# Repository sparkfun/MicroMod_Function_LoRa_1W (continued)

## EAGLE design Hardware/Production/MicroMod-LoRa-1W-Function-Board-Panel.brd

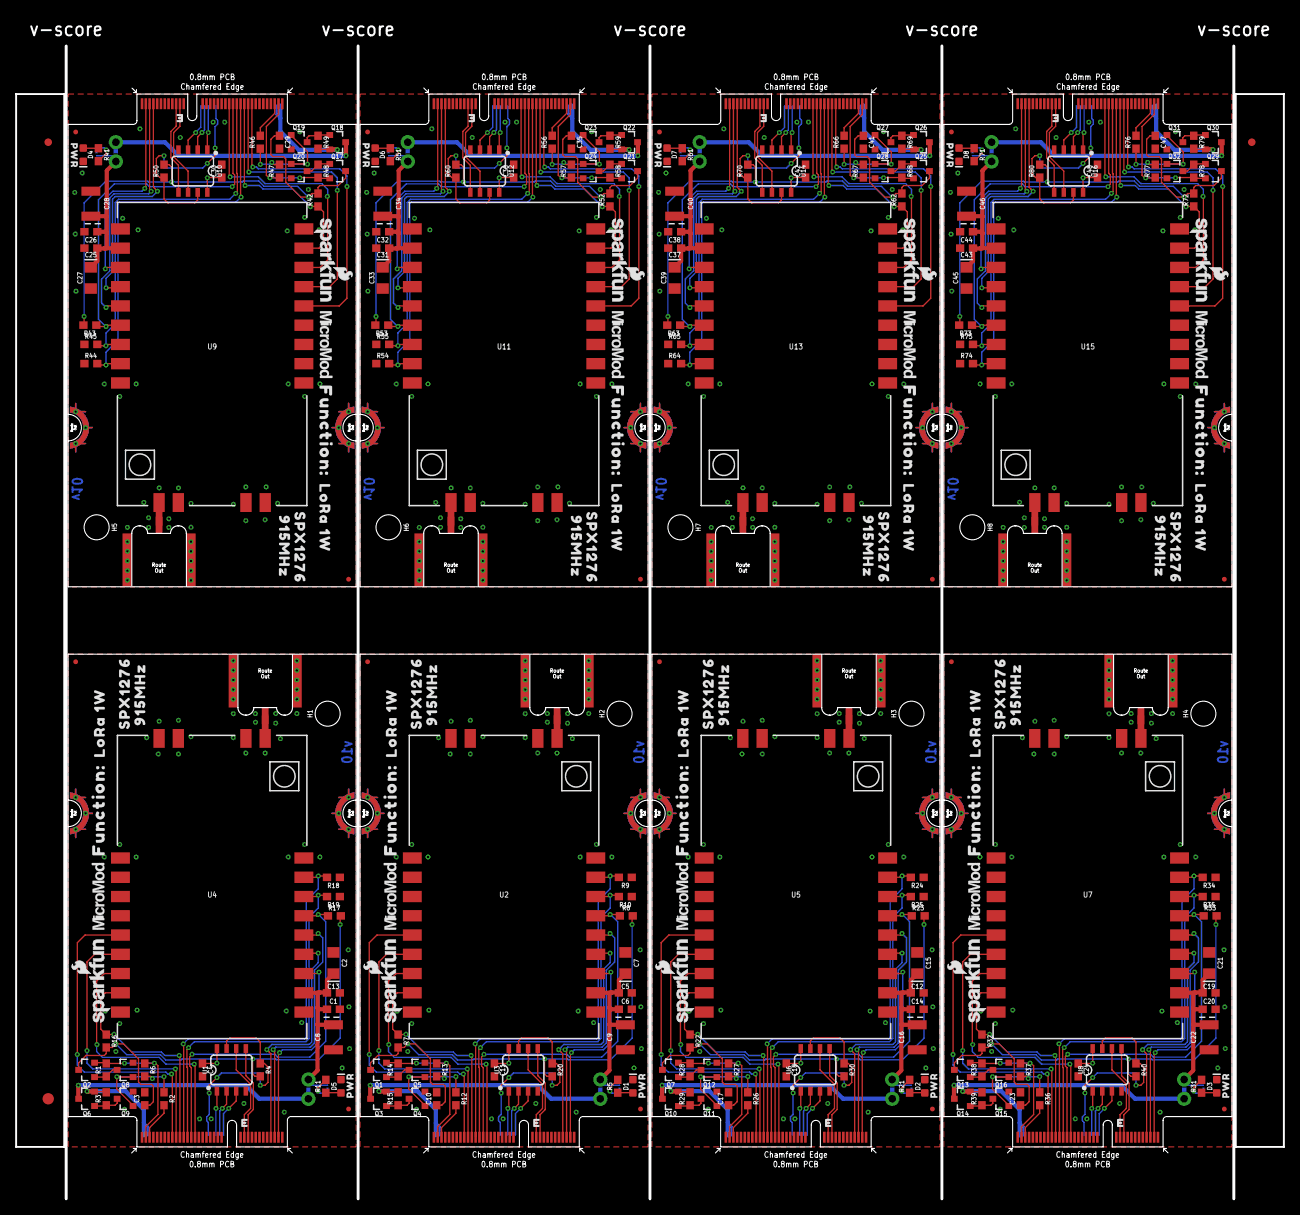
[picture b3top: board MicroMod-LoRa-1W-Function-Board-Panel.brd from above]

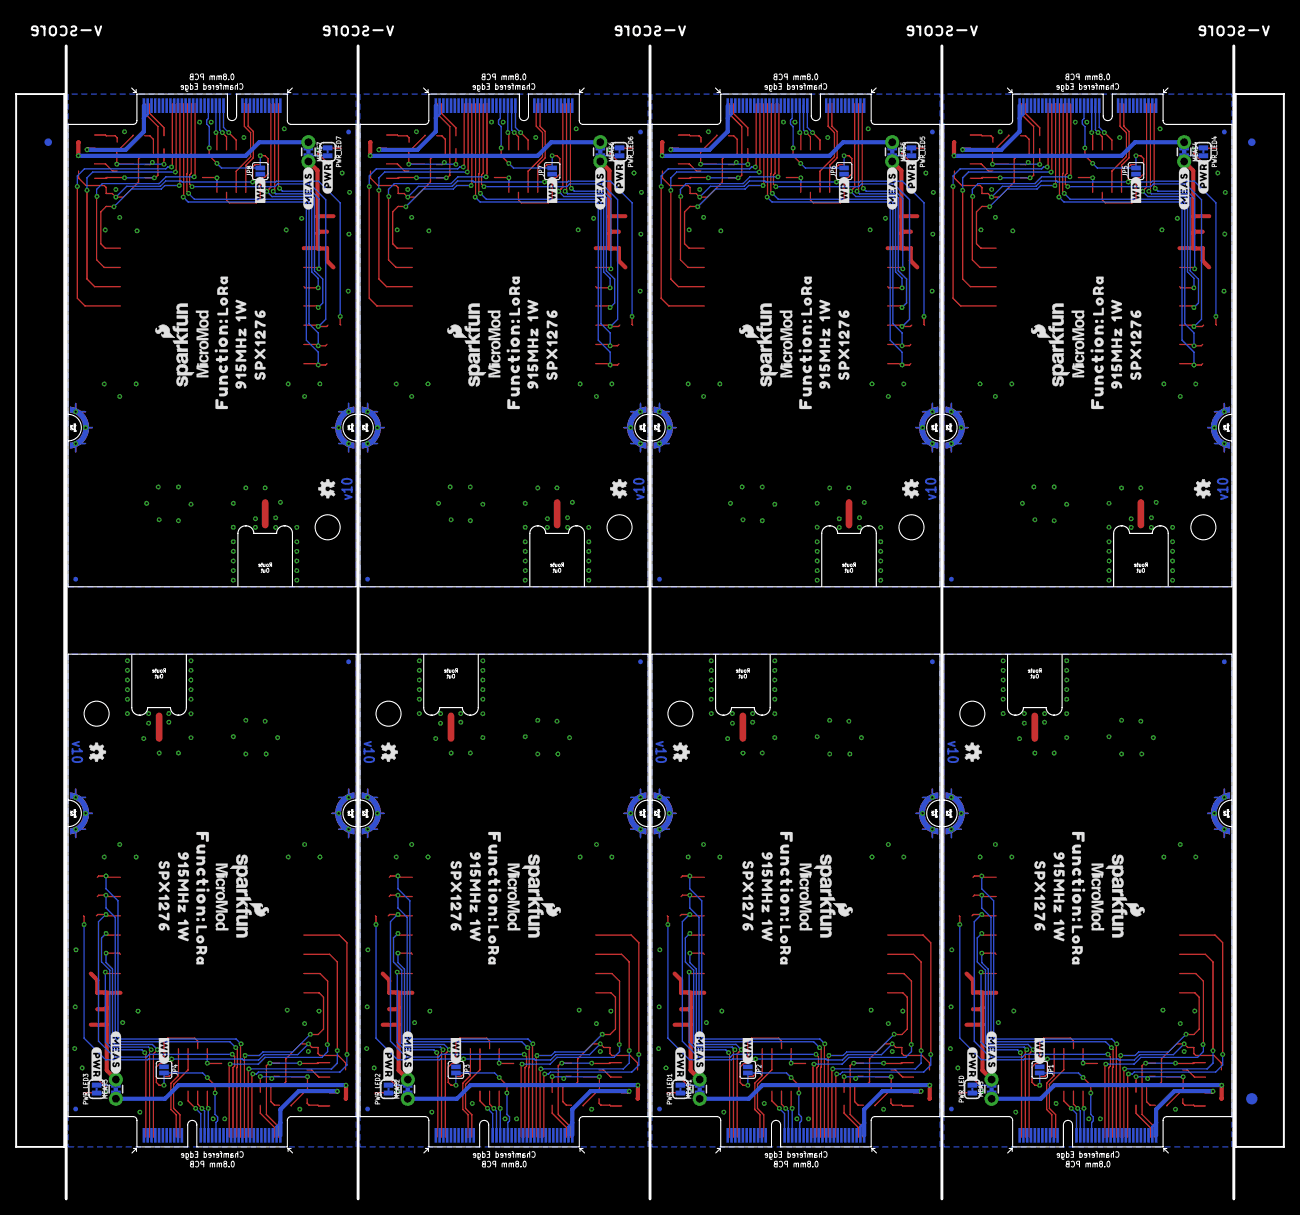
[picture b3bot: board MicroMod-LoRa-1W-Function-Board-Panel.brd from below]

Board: 2 copper layers, 167.1 x 156.0 mm, 422 parts (131 on the bottom side), 232 nets.

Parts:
C1, C3, C4, C6, C10, C11, C14, C17, C18, C20, C23, C24, C26, C29, C30, C32, C35, C36, C38, C41, C42, C44, C47, C48: 0.1uF; 0603
C2, C7, C15, C21, C27, C33, C39, C45: 10uF; EIA3216
C5, C12, C13, C19, C25, C31, C37, C43: 0.22uF; 0603
C8, C9, C16, C22, C28, C34, C40, C46: 47uF; EIA3528
D1, D2, D3, D4, D5, D6, D7, D8: RED; LED-0603
E1, E2, E3, E4, E5, E6, E7, E8: RP-SMA; SMA-EDGE-SMD
E$1, E$2, E$3, E$4: FIDUCIAL-1X2
E$5, E$6: FIDUCIAL-1.5X3
FD1, FD2, FD3, FD4, FD5, FD6, FD7, FD8, FD9, FD10, FD11, FD12, FD13, FD14, FD15, FD16, FD17, FD18, FD19, FD20, FD21, FD22, FD23, FD24, FD25, FD26, FD27, FD28, FD29, FD30, FD31, FD32: FIDUCIALUFIDUCIAL; FIDUCIAL-MICRO
H1, H2, H3, H4, H5, H6, H7, H8: STAND-OFF
J1, J2, J3, J4, J5, J6, J7, J11: MICROMOD_STANDARD; M.2-CARD-E-22_FUNCTION_STANDARD
JP1, JP2, JP3, JP4, JP5, JP6, JP7, JP8: JUMPER-SMT_2_NO_SILK; SMT-JUMPER_2_NO_SILK
LOGO1, LOGO2, LOGO4, LOGO6, LOGO7, LOGO9, LOGO10, LOGO12, LOGO13, LOGO15, LOGO16, LOGO18, LOGO19, LOGO21, LOGO22, LOGO24: SFE_LOGO_NAME_FLAME.1_INCH; SFE_LOGO_NAME_FLAME_.1
LOGO3, LOGO5, LOGO8, LOGO11, LOGO14, LOGO17, LOGO20, LOGO23: OSHW-LOGOMINI; OSHW-LOGO-MINI
MEAS, MEAS1, MEAS2, MEAS3, MEAS4, MEAS5, MEAS6, MEAS7: JUMPER-COMBO_2_NC_TRACE; COMBO-JUMPER_2_NC_TRACE
PWR_LED, PWR_LED1, PWR_LED2, PWR_LED3, PWR_LED4, PWR_LED5, PWR_LED6, PWR_LED7: JUMPER-SMT_2_NC_TRACE_SILK; SMT-JUMPER_2_NC_TRACE_SILK
Q1, Q2, Q3, Q6, Q7, Q10, Q13, Q14, Q17, Q18, Q21, Q22, Q25, Q26, Q29, Q30: 20V/4.2A/52mΩ/1.4W; SOT23-3
Q4, Q5, Q8, Q9, Q11, Q12, Q15, Q16, Q19, Q20, Q23, Q24, Q27, Q28, Q31, Q32: 5.8A/30V/35mΩ; SOT23-3
R1, R3, R4, R14, R15, R20, R28, R29, R30, R38, R39, R40, R48, R49, R50, R58, R59, R60, R68, R69, R70, R78, R79, R80: 10k; 0603
R2, R12, R26, R36, R46, R56, R66, R76: 470; 0603
R5, R11, R21, R31, R41, R51, R61, R71: 1k; 0603
R6, R7, R8, R9, R10, R13, R16, R17, R18, R19, R22, R23, R24, R25, R27, R32, R33, R34, R35, R37, R42, R43, R44, R45, R47, R52, R53, R54, R55, R57, R62, R63, R64, R65, R67, R72, R73, R74, R75, R77: 100k; 0603
U1, U3, U6, U8, U10, U12, U14, U16: EEPROM; SO08
U2, U4, U5, U7, U9, U11, U13, U15: E19-915M30S; E19-915MS1W
U$1, U$5, U$16, U$19, U$36, U$40, U$53, U$56, U$70, U$73, U$86, U$89, U$102, U$105, U$118, U$121: LORA0
U$2, U$14, U$22, U$30, U$34, U$43, U$51, U$59, U$68, U$76, U$84, U$92, U$100, U$108, U$116, U$124: 1W1
U$3, U$15, U$21, U$29, U$35, U$42, U$52, U$58, U$69, U$75, U$85, U$91, U$101, U$107, U$117, U$123: 915MHZ2
U$4, U$8, U$23, U$25, U$44, U$46, U$60, U$62, U$77, U$79, U$93, U$95, U$109, U$111, U$125, U$127: FUNCTION#0
U$6, U$17, U$20, U$27, U$38, U$41, U$54, U$57, U$71, U$74, U$87, U$90, U$103, U$106, U$119, U$122: SPX12763
U$7, U$18, U$39, U$55, U$72, U$88, U$104, U$120: PWR0
U$9, U$24, U$45, U$61, U$78, U$94, U$110, U$126: #PWR#0
U$10, U$26, U$47, U$64, U$80, U$96, U$112, U$128: #WP#0
U$11, U$12, U$31, U$32, U$37, U$48, U$49, U$63, U$65, U$66, U$81, U$82, U$97, U$98, U$113, U$114: MICROMOD_LOGO_.35
U$13, U$28, U$33, U$50, U$67, U$83, U$99, U$115: #MEAS#3

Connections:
3.3V: C3.1, C4.1, Q2.3, R4.2, R16.2, R17.2, U1.8
3.3V1: C10.1, C11.1, Q1.3, R7.2, R8.2, R20.2, U3.8
3.3V2: C17.1, C18.1, Q7.3, R22.2, R23.2, R30.2, U6.8
3.3V3: C23.1, C24.1, Q13.3, R32.2, R33.2, R40.2, U8.8
3.3V4: C29.1, C30.1, Q17.3, R42.2, R43.2, R50.2, U10.8
3.3V5: C35.1, C36.1, Q21.3, R52.2, R53.2, R60.2, U12.8
3.3V6: C41.1, C42.1, Q25.3, R62.2, R63.2, R70.2, U14.8
3.3V7: C47.1, C48.1, Q29.3, R72.2, R73.2, R80.2, U16.8
3.3V_IN: J11.73, Q2.2, R1.2, R6.1
3.3V_IN1: J1.73, Q1.2, R13.1, R14.2
3.3V_IN2: J2.73, Q7.2, R27.1, R28.2
3.3V_IN3: J3.73, Q13.2, R37.1, R38.2
3.3V_IN4: J4.73, Q17.2, R47.1, R48.2
3.3V_IN5: J5.73, Q21.2, R57.1, R58.2
3.3V_IN6: J6.73, Q25.2, R67.1, R68.2
3.3V_IN7: J7.73, Q29.2, R77.1, R78.2
5V: C1.1, C2.+, C8.A, C13.1, MEAS.2, MEAS.4, PWR_LED.2, U4.11
5V1: C5.1, C6.1, C7.+, C9.A, MEAS1.2, MEAS1.4, PWR_LED1.2, U2.11
5V2: C12.1, C14.1, C15.+, C16.A, MEAS2.2, MEAS2.4, PWR_LED2.2, U5.11
5V3: C19.1, C20.1, C21.+, C22.A, MEAS3.2, MEAS3.4, PWR_LED3.2, U7.11
5V4: C25.1, C26.1, C27.+, C28.A, MEAS4.2, MEAS4.4, PWR_LED4.2, U9.11
5V5: C31.1, C32.1, C33.+, C34.A, MEAS5.2, MEAS5.4, PWR_LED5.2, U11.11
5V6: C37.1, C38.1, C39.+, C40.A, MEAS6.2, MEAS6.4, PWR_LED6.2, U13.11
5V7: C43.1, C44.1, C45.+, C46.A, MEAS7.2, MEAS7.4, PWR_LED7.2, U15.11
A0: J11.36, U1.1
A1: J11.34, U1.2
A2: J11.32, U1.3
A3: J1.36, U3.1
A4: J1.32, U3.3
A5: J1.34, U3.2
A6: J2.36, U6.1
A7: J2.32, U6.3
A8: J2.34, U6.2
A9: J3.36, U8.1
A10: J3.32, U8.3
A11: J3.34, U8.2
A12: J4.36, U10.1
A13: J4.32, U10.3
A14: J4.34, U10.2
A15: J5.36, U12.1
A16: J5.32, U12.3
A17: J5.34, U12.2
A18: J6.36, U14.1
A19: J6.32, U14.3
A20: J6.34, U14.2
A21: J7.36, U16.1
A22: J7.32, U16.3
A23: J7.34, U16.2
EWP: J11.40, JP1.2, R4.1, U1.7
EWP1: J1.40, JP2.2, R20.1, U3.7
EWP2: J2.40, JP3.2, R30.1, U6.7
EWP3: J3.40, JP4.2, R40.1, U8.7
EWP4: J4.40, JP5.2, R50.1, U10.7
EWP5: J5.40, JP6.2, R60.1, U12.7
EWP6: J6.40, JP7.2, R70.1, U14.7
EWP7: J7.40, JP8.2, R80.1, U16.7
GND: C1.2, C2.-, C3.2, C4.2, C8.C, C13.2, D5.C, E1.GND@0, E1.GND@1, J11.1, J11.33, J11.39, J11.45, J11.75, J11.GND1, J11.GND2, J11.GND3, J11.GND4, J11.GND5, J11.GND6, JP1.1, Q8.2, Q9.2, R18.1, R19.1, U1.4, U4.1, U4.9, U4.10, U4.18, U4.20, U4.21, U4.22
GND1: C5.2, C6.2, C7.-, C9.C, C10.2, C11.2, D1.C, E2.GND@0, E2.GND@1, J1.1, J1.33, J1.39, J1.45, J1.75, J1.GND1, J1.GND2, J1.GND3, J1.GND4, J1.GND5, J1.GND6, JP2.1, Q4.2, Q5.2, R9.1, R10.1, U2.1, U2.9, U2.10, U2.18, U2.20, U2.21, U2.22, U3.4
GND2: C12.2, C14.2, C15.-, C16.C, C17.2, C18.2, D2.C, E3.GND@0, E3.GND@1, J2.1, J2.33, J2.39, J2.45, J2.75, J2.GND1, J2.GND2, J2.GND3, J2.GND4, J2.GND5, J2.GND6, JP3.1, Q11.2, Q12.2, R24.1, R25.1, U5.1, U5.9, U5.10, U5.18, U5.20, U5.21, U5.22, U6.4
GND3: C19.2, C20.2, C21.-, C22.C, C23.2, C24.2, D3.C, E4.GND@0, E4.GND@1, J3.1, J3.33, J3.39, J3.45, J3.75, J3.GND1, J3.GND2, J3.GND3, J3.GND4, J3.GND5, J3.GND6, JP4.1, Q15.2, Q16.2, R34.1, R35.1, U7.1, U7.9, U7.10, U7.18, U7.20, U7.21, U7.22, U8.4
GND4: C25.2, C26.2, C27.-, C28.C, C29.2, C30.2, D4.C, E5.GND@0, E5.GND@1, J4.1, J4.33, J4.39, J4.45, J4.75, J4.GND1, J4.GND2, J4.GND3, J4.GND4, J4.GND5, J4.GND6, JP5.1, Q19.2, Q20.2, R44.1, R45.1, U9.1, U9.9, U9.10, U9.18, U9.20, U9.21, U9.22, U10.4
GND5: C31.2, C32.2, C33.-, C34.C, C35.2, C36.2, D6.C, E6.GND@0, E6.GND@1, J5.1, J5.33, J5.39, J5.45, J5.75, J5.GND1, J5.GND2, J5.GND3, J5.GND4, J5.GND5, J5.GND6, JP6.1, Q23.2, Q24.2, R54.1, R55.1, U11.1, U11.9, U11.10, U11.18, U11.20, U11.21, U11.22, U12.4
GND6: C37.2, C38.2, C39.-, C40.C, C41.2, C42.2, D7.C, E7.GND@0, E7.GND@1, J6.1, J6.33, J6.39, J6.45, J6.75, J6.GND1, J6.GND2, J6.GND3, J6.GND4, J6.GND5, J6.GND6, JP7.1, Q27.2, Q28.2, R64.1, R65.1, U13.1, U13.9, U13.10, U13.18, U13.20, U13.21, U13.22, U14.4
GND7: C43.2, C44.2, C45.-, C46.C, C47.2, C48.2, D8.C, E8.GND@0, E8.GND@1, J7.1, J7.33, J7.39, J7.45, J7.75, J7.GND1, J7.GND2, J7.GND3, J7.GND4, J7.GND5, J7.GND6, JP8.1, Q31.2, Q32.2, R74.1, R75.1, U15.1, U15.9, U15.10, U15.18, U15.20, U15.21, U15.22, U16.4
I2C_SCL: J11.21, U1.6
I2C_SCL1: J1.21, U3.6
I2C_SCL2: J2.21, U6.6
I2C_SCL3: J3.21, U8.6
I2C_SCL4: J4.21, U10.6
I2C_SCL5: J5.21, U12.6
I2C_SCL6: J6.21, U14.6
I2C_SCL7: J7.21, U16.6
I2C_SDA: J11.19, U1.5
I2C_SDA1: J1.19, U3.5
I2C_SDA2: J2.19, U6.5
I2C_SDA3: J3.19, U8.5
I2C_SDA4: J4.19, U10.5
I2C_SDA5: J5.19, U12.5
I2C_SDA6: J6.19, U14.5
I2C_SDA7: J7.19, U16.5
LORA_!CS!: J11.49, R17.1, U4.15
LORA_!CS!1: J1.49, R8.1, U2.15
LORA_!CS!2: J2.49, R23.1, U5.15
LORA_!CS!3: J3.49, R33.1, U7.15
LORA_!CS!4: J4.49, R43.1, U9.15
LORA_!CS!5: J5.49, R53.1, U11.15
LORA_!CS!6: J6.49, R63.1, U13.15
LORA_!CS!7: J7.49, R73.1, U15.15
LORA_!RST!: J11.55, R16.1, U4.8
LORA_!RST!1: J1.55, R7.1, U2.8
LORA_!RST!2: J2.55, R22.1, U5.8
LORA_!RST!3: J3.55, R32.1, U7.8
LORA_!RST!4: J4.55, R42.1, U9.8
LORA_!RST!5: J5.55, R52.1, U11.8
LORA_!RST!6: J6.55, R62.1, U13.8
LORA_!RST!7: J7.55, R72.1, U15.8
LORA_D0: J11.47, U4.7
LORA_D1: J11.57, U4.6
LORA_D2: J11.59, U4.5
LORA_D3: J1.47, U2.7
LORA_D4: J1.57, U2.6
LORA_D5: J1.59, U2.5
LORA_D6: J2.47, U5.7
LORA_D7: J2.57, U5.6
LORA_D8: J2.59, U5.5
LORA_D9: J3.47, U7.7
LORA_D10: J3.57, U7.6
LORA_D11: J3.59, U7.5
LORA_D12: J4.47, U9.7
LORA_D13: J4.57, U9.6
LORA_D14: J4.59, U9.5
LORA_D15: J5.47, U11.7
LORA_D16: J5.57, U11.6
LORA_D17: J5.59, U11.5
LORA_D18: J6.47, U13.7
LORA_D19: J6.57, U13.6
LORA_D20: J6.59, U13.5
LORA_D21: J7.47, U15.7
LORA_D22: J7.57, U15.6
LORA_D23: J7.59, U15.5
LORA_RXEN: J11.53, R18.2, U4.17
LORA_RXEN1: J1.53, R9.2, U2.17
LORA_RXEN2: J2.53, R24.2, U5.17
LORA_RXEN3: J3.53, R34.2, U7.17
LORA_RXEN4: J4.53, R44.2, U9.17
LORA_RXEN5: J5.53, R54.2, U11.17
LORA_RXEN6: J6.53, R64.2, U13.17
LORA_RXEN7: J7.53, R74.2, U15.17
LORA_TXEN: J11.51, R19.2, U4.16
LORA_TXEN1: J1.51, R10.2, U2.16
LORA_TXEN2: J2.51, R25.2, U5.16
LORA_TXEN3: J3.51, R35.2, U7.16
LORA_TXEN4: J4.51, R45.2, U9.16
LORA_TXEN5: J5.51, R55.2, U11.16
LORA_TXEN6: J6.51, R65.2, U13.16
LORA_TXEN7: J7.51, R75.2, U15.16
unnamed: E1.SIG, U4.19
unnamed: Q2.1, Q8.3, R1.1
unnamed: Q6.1, Q9.3, R3.1
unnamed: J11.71, R2.2
unnamed: D5.A, R11.1
unnamed: PWR_LED.1, R11.2
unnamed: PWR_LED1.1, R5.2
unnamed: D1.A, R5.1
unnamed: E2.SIG, U2.19
unnamed: J1.71, R12.2
unnamed: Q1.1, Q5.3, R14.1
unnamed: Q3.1, Q4.3, R15.1
unnamed: PWR_LED2.1, R21.2
unnamed: D2.A, R21.1
unnamed: E3.SIG, U5.19
unnamed: J2.71, R26.2
unnamed: Q7.1, Q12.3, R28.1
unnamed: Q10.1, Q11.3, R29.1
unnamed: PWR_LED3.1, R31.2
unnamed: D3.A, R31.1
unnamed: E4.SIG, U7.19
unnamed: J3.71, R36.2
unnamed: Q13.1, Q16.3, R38.1
unnamed: Q14.1, Q15.3, R39.1
unnamed: PWR_LED4.1, R41.2
unnamed: D4.A, R41.1
unnamed: E5.SIG, U9.19
unnamed: J4.71, R46.2
unnamed: Q17.1, Q20.3, R48.1
unnamed: Q18.1, Q19.3, R49.1
unnamed: PWR_LED5.1, R51.2
unnamed: D6.A, R51.1
unnamed: E6.SIG, U11.19
unnamed: J5.71, R56.2
unnamed: Q21.1, Q24.3, R58.1
unnamed: Q22.1, Q23.3, R59.1
unnamed: PWR_LED6.1, R61.2
unnamed: D7.A, R61.1
unnamed: E7.SIG, U13.19
unnamed: J6.71, R66.2
unnamed: Q25.1, Q28.3, R68.1
unnamed: Q26.1, Q27.3, R69.1
unnamed: PWR_LED7.1, R71.2
unnamed: D8.A, R71.1
unnamed: E8.SIG, U15.19
unnamed: J7.71, R76.2
unnamed: Q29.1, Q32.3, R78.1
unnamed: Q30.1, Q31.3, R79.1
PWR_EN: Q8.1, Q9.1, R2.1, R6.2
PWR_EN1: Q4.1, Q5.1, R12.1, R13.2
PWR_EN2: Q11.1, Q12.1, R26.1, R27.2
PWR_EN3: Q15.1, Q16.1, R36.1, R37.2
PWR_EN4: Q19.1, Q20.1, R46.1, R47.2
PWR_EN5: Q23.1, Q24.1, R56.1, R57.2
PWR_EN6: Q27.1, Q28.1, R66.1, R67.2
PWR_EN7: Q31.1, Q32.1, R76.1, R77.2
SPI_CIPO: J11.7, U4.13
SPI_CIPO1: J1.7, U2.13
SPI_CIPO2: J2.7, U5.13
SPI_CIPO3: J3.7, U7.13
SPI_CIPO4: J4.7, U9.13
SPI_CIPO5: J5.7, U11.13
SPI_CIPO6: J6.7, U13.13
SPI_CIPO7: J7.7, U15.13
SPI_COPI: J11.5, U4.14
SPI_COPI1: J1.5, U2.14
SPI_COPI2: J2.5, U5.14
SPI_COPI3: J3.5, U7.14
SPI_COPI4: J4.5, U9.14
SPI_COPI5: J5.5, U11.14
SPI_COPI6: J6.5, U13.14
SPI_COPI7: J7.5, U15.14
SPI_SCK: J11.3, U4.12
SPI_SCK1: J1.3, U2.12
SPI_SCK2: J2.3, U5.12
SPI_SCK3: J3.3, U7.12
SPI_SCK4: J4.3, U9.12
SPI_SCK5: J5.3, U11.12
SPI_SCK6: J6.3, U13.12
SPI_SCK7: J7.3, U15.12
VCC: MEAS.1, MEAS.3, Q6.3
VCC1: MEAS1.1, MEAS1.3, Q3.3
VCC2: MEAS2.1, MEAS2.3, Q10.3
VCC3: MEAS3.1, MEAS3.3, Q14.3
VCC4: MEAS4.1, MEAS4.3, Q18.3
VCC5: MEAS5.1, MEAS5.3, Q22.3
VCC6: MEAS6.1, MEAS6.3, Q26.3
VCC7: MEAS7.1, MEAS7.3, Q30.3
VCC_IN: J11.72, J11.74, Q6.2, R3.2
VCC_IN1: J1.72, J1.74, Q3.2, R15.2
VCC_IN2: J2.72, J2.74, Q10.2, R29.2
VCC_IN3: J3.72, J3.74, Q14.2, R39.2
VCC_IN4: J4.72, J4.74, Q18.2, R49.2
VCC_IN5: J5.72, J5.74, Q22.2, R59.2
VCC_IN6: J6.72, J6.74, Q26.2, R69.2
VCC_IN7: J7.72, J7.74, Q30.2, R79.2

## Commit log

2021-07-21 Remove local copy of library
2021-07-21 Remove old files. Add ignore.
2021-09-07 Adding panel files
2021-09-20 Fix power control circuit. Add example sketch. Add x02 production panels.
2021-09-23 Add WP access to card edge.
2021-09-23 Update version to v10.
2021-11-01 Add SMA center pin. Increase panel gap to facilitate center pin. PCB is still v10.
2021-11-11 Updates the design to use the Micromod-function device in the official SFE Eagle Libs
2021-11-11 Add ReadMe and License files
2021-11-11 Update README.md
    Added in supported Arduino libraries and hardware datasheets
2022-05-04 Update README.md
    Fix production folder location
